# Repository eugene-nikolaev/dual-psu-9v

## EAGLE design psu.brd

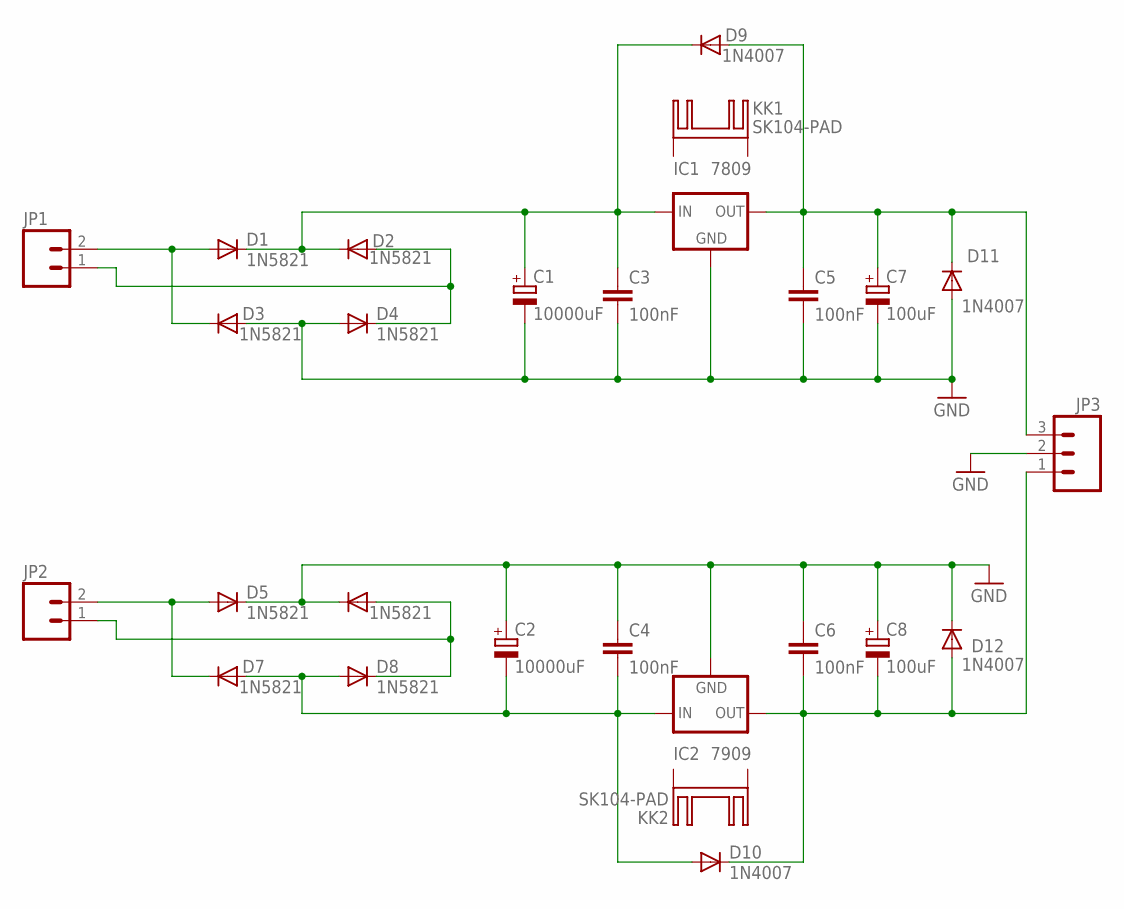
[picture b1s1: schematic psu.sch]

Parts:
C1, C2: 10000uF; E7,5-18
C3, C4, C5, C6: 100nF; C025-025X050
C7, C8: 100uF; E2,5-7
D1, D2, D3, D4, D5, D6, D7, D8: 1N5821; DO201-15
D9, D10, D11, D12: 1N4007; DO41-10
IC1: 7809; 78XXS
IC2: 7909; 79XXS
JP1, JP2: M025MM; SCREWTERMINAL-5MM-2
JP3: M03-SCREW-5MM; SCREWTERMINAL-5MM-3
KK1, KK2: SK104-PAD

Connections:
GND: C1.-, C2.+, C3.2, C4.1, C5.2, C6.1, C7.-, C8.+, D3.A, D4.A, D5.C, D6.C, D11.A, D12.C, IC1.GND, IC2.GND, JP3.2
IN1_AC_A: D1.A, D3.C, JP1.2
IN1_AC_B: D2.A, D4.C, JP1.1
IN2_AC_A: D5.A, D7.C, JP2.2
IN2_AC_B: D6.A, D8.C, JP2.1
unnamed: C1.+, C3.1, D1.C, D2.C, D9.C, IC1.IN
unnamed: C2.-, C4.2, D7.A, D8.A, D10.A, IC2.IN
OUT_NEG: C6.2, C8.-, D10.C, D12.A, IC2.OUT, JP3.1
OUT_POS: C5.1, C7.+, D9.A, D11.C, IC1.OUT, JP3.3

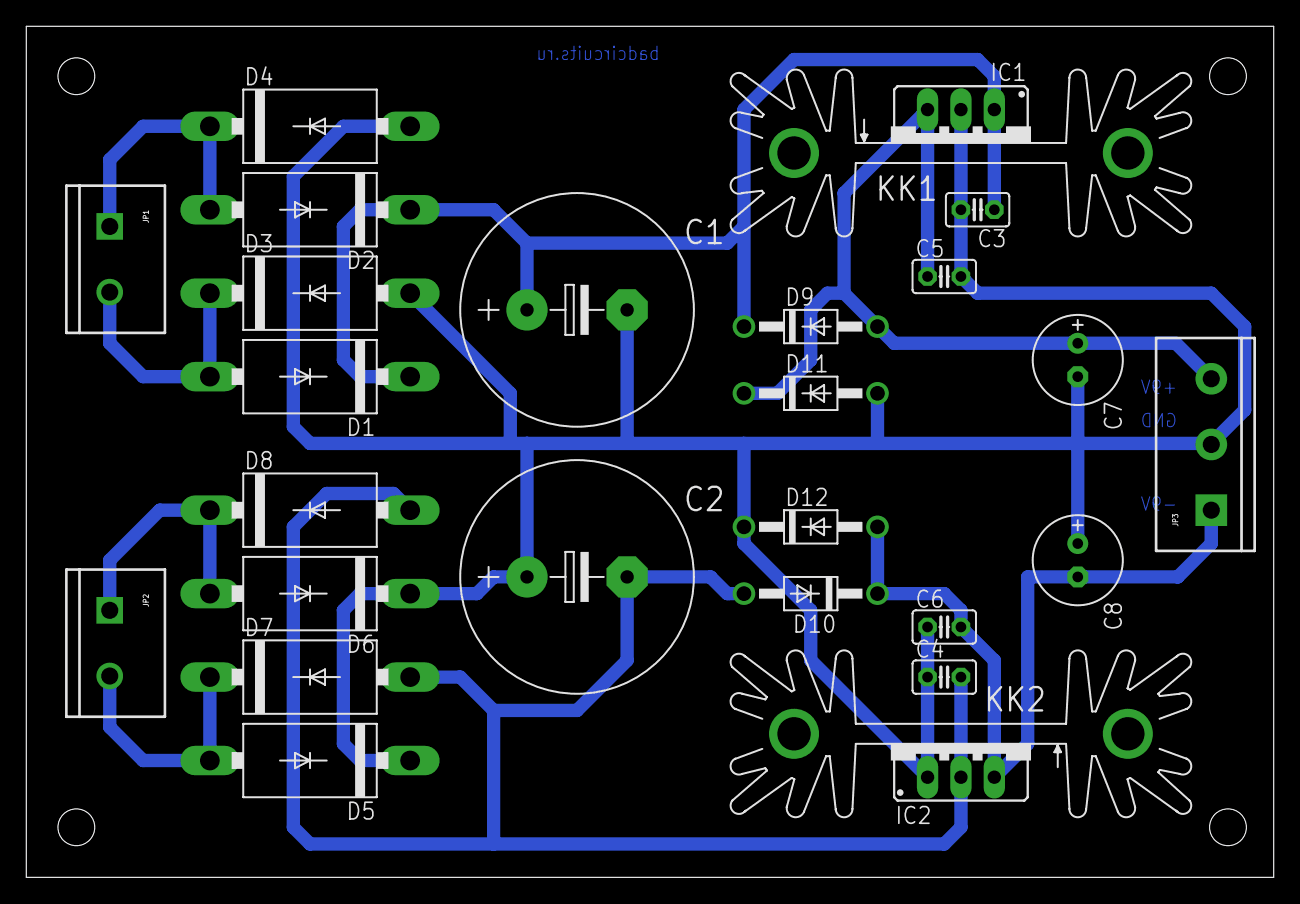
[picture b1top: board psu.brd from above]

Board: 2 copper layers, 94.9 x 64.8 mm, 27 parts (0 on the bottom side), 9 nets.

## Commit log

2015-11-25 Initial commit - components placed
2015-11-25 Positive hand traced
2015-11-25 Routed!

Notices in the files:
parts and their libraries:
SparkFun-Connectors: Licensing: Creative Commons ShareAlike 4.0 International - https://creativecommons.org/licenses/by-sa/4.0
